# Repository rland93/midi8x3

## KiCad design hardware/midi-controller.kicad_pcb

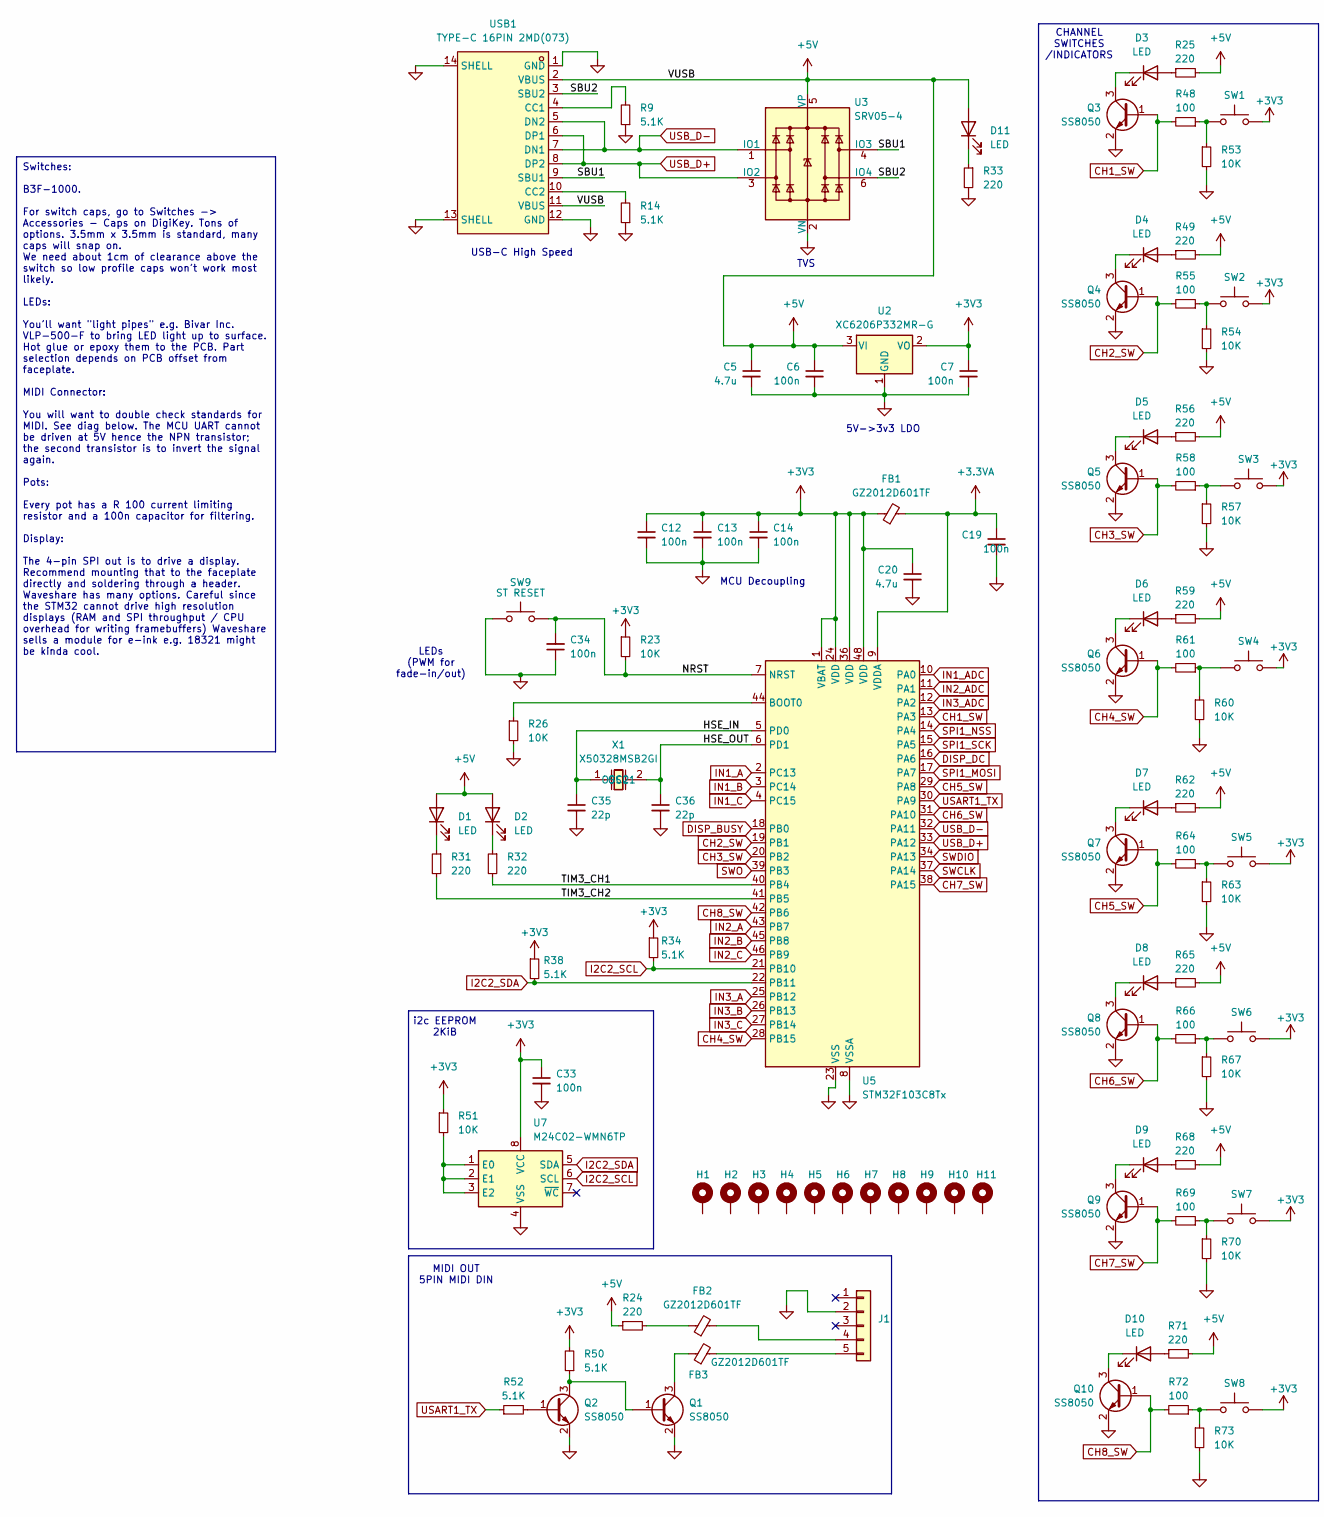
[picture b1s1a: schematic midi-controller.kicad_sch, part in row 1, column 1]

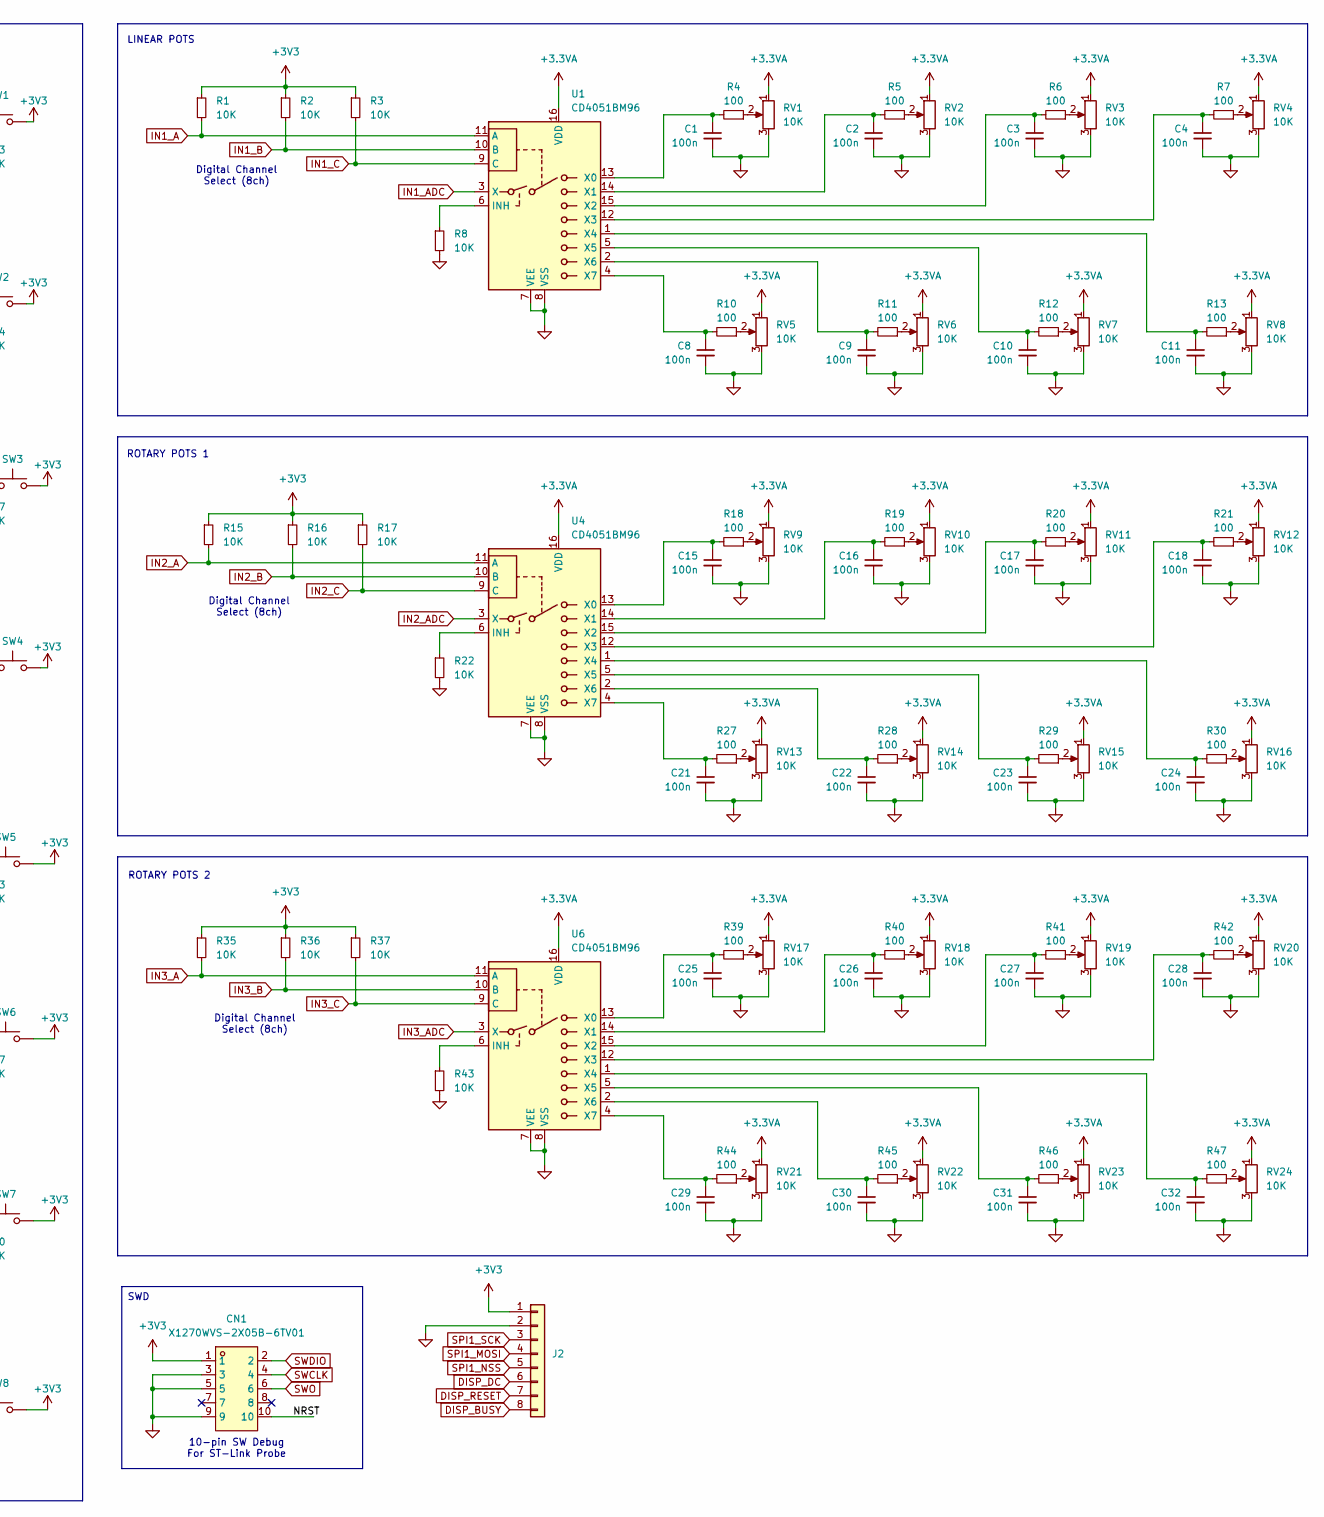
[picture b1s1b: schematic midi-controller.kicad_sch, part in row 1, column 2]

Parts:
C1, C2, C3, C4, C6, C7, C8, C9, C10, C11, C12, C13, C14, C15, C16, C17, C18, C19, C21, C22, C23, C24, C25, C26, C27, C28, C29, C30, C31, C32, C33, C34: 100n; C_0402_1005Metric; LCSC ID C14663
C5, C20: 4.7u; C_0603_1608Metric; LCSC ID C19666
C35, C36: 22p; C_0402_1005Metric
CN1: X1270WVS-2X05B-6TV01; IDC-SMD_10P-P1.27_X1270WVS-2X05B-6TV01; LCSC Part Extended
D1, D2, D3, D4, D5, D6, D7, D8, D9, D10, D11: LED; LED_0603_1608Metric; LCSC ID C2286
FB1, FB2, FB3: GZ2012D601TF; L_0805_2012Metric; LCSC ID C1017
H1, H2, H3, H4, H5, H6, H7, H8, H9, H10, H11: MountingHole_Pad; MountingHole_2.7mm_M2.5_DIN965_Pad
J1: Conn_01x05; PinHeader_1x05_P2.54mm_Vertical; LCSC ID None
J2: Conn_01x08; JST_PH_B8B-PH-K_1x08_P2.00mm_Vertical
Q1, Q2, Q3, Q4, Q5, Q6, Q7, Q8, Q9, Q10: SS8050; SOT-23; LCSC ID C2150
R1, R2, R3, R8, R15, R16, R17, R22, R23, R26, R35, R36, R37, R43, R51, R53, R54, R57, R60, R63, R67, R70, R73: 10K; R_0402_1005Metric; LCSC ID C25744
R4, R5, R6, R7, R10, R11, R12, R13, R18, R19, R20, R21, R27, R28, R29, R30, R39, R40, R41, R42, R44, R45, R46, R47, R48, R55, R58, R61, R64, R66, R69, R72: 100; R_0603_1608Metric; LCSC ID C22775
R9, R14, R34, R38, R50, R52: 5.1K; R_0402_1005Metric; LCSC ID C25905
R24, R25, R31, R32, R33, R49, R56, R59, R62, R65, R68, R71: 220; R_0603_1608Metric; LCSC ID C22962
RV1, RV2, RV3, RV4, RV5, RV6, RV7, RV8: 10K; Potentiometer_Bourns_PTA6043_Single_Slide; Digikey/Part PTA6043-2015DPB103
RV9, RV10, RV11, RV12, RV13, RV14, RV15, RV16, RV17, RV18, RV19, RV20, RV21, RV22, RV23, RV24: 10K; Potentiometer_Bourns_PTV09A-1_Single_Vertical; Digikey/Part PTV09A-4025S-A103
SW1, SW2, SW3, SW4, SW5, SW6, SW7, SW8: SW_Push; SW_TH_Tactile_Omron_B3F-10xx
SW9: ST RESET; SW_TH_Tactile_Omron_B3F-10xx; LCSC Part None
U1, U4, U6: CD4051BM96; SOIC-16_3.9x9.9mm_P1.27mm; LCSC ID C21379
U2: XC6206P332MR-G; SOT-23-3; LCSC ID C5446
U3: SRV05-4; SOT-23-6; LCSC ID C7420376
U5: STM32F103C8Tx; LQFP-48_7x7mm_P0.5mm; LCSC ID C8734
U7: M24C02-WMN6TP; SOIC-8_3.9x4.9mm_P1.27mm; LCSC ID C7562
USB1: TYPE-C 16PIN 2MD(073); USB-C-SMD_TYPE-C-6PIN-2MD-073; LCSC Part Extended
X1: X50328MSB2GI; CRYSTAL-SMD_L5.0-W3.2; LCSC Part C115962

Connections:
+3.3VA: C19.1, FB1.2, RV1.1, RV2.1, RV3.1, RV4.1, RV5.1, RV6.1, RV7.1, RV8.1, RV9.1, RV10.1, RV11.1, RV12.1, RV13.1, RV14.1, RV15.1, RV16.1, RV17.1, RV18.1, RV19.1, RV20.1, RV21.1, RV22.1, RV23.1, RV24.1, U1.16 (VDD), U4.16 (VDD), U5.9 (VDDA), U6.16 (VDD)
+3V3: C7.1, C12.1, C13.1, C14.1, C20.1, C33.1, CN1.1, FB1.1, J2.1, R1.1, R2.1, R3.1, R15.1, R16.1, R17.1, R23.1, R34.1, R35.1, R36.1, R37.1, R38.1, R50.2, R51.1, SW1.2, SW2.2, SW3.2, SW4.2, SW5.2, SW6.2, SW7.2, SW8.2, U2.2 (VO), U5.1 (VBAT), U5.24 (VDD), U5.36 (VDD), U5.48 (VDD), U7.8 (VCC)
+5V: C5.1, C6.1, D1.2 (A), D2.2 (A), D11.2 (A), R24.1, R25.2, R49.2, R56.2, R59.2, R62.2, R65.2, R68.2, R71.2, U2.3 (VI), U3.5 (VP), USB1.2 (VBUS), USB1.11 (VBUS)
/HSE_IN: C35.1, U5.5 (PD0), X1.1 (OSC1)
/HSE_OUT: C36.1, U5.6 (PD1), X1.2 (OSC2)
/NRST: C34.2, CN1.10, R23.2, SW9.2, U5.7 (NRST)
/SBU1: U3.4 (IO3), USB1.9 (SBU1)
/SBU2: U3.6 (IO4), USB1.3 (SBU2)
/TIM3_CH1: R32.2, U5.40 (PB4)
/TIM3_CH2: R31.2, U5.41 (PB5)
CH1_SW: Q3.1 (B), R48.2, U5.13 (PA3)
CH2_SW: Q4.1 (B), R55.2, U5.19 (PB1)
CH3_SW: Q5.1 (B), R58.2, U5.20 (PB2)
CH4_SW: Q6.1 (B), R61.2, U5.28 (PB15)
CH5_SW: Q7.1 (B), R64.2, U5.29 (PA8)
CH6_SW: Q8.1 (B), R66.2, U5.31 (PA10)
CH7_SW: Q9.1 (B), R69.2, U5.38 (PA15)
CH8_SW: Q10.1 (B), R72.2, U5.42 (PB6)
DISP_BUSY: J2.8, U5.18 (PB0)
DISP_DC: J2.6, U5.16 (PA6)
DISP_RESET: J2.7
GND: C1.2, C2.2, C3.2, C4.2, C5.2, C6.2, C7.2, C8.2, C9.2, C10.2, C11.2, C12.2, C13.2, C14.2, C15.2, C16.2, C17.2, C18.2, C19.2, C20.2, C21.2, C22.2, C23.2, C24.2, C25.2, C26.2, C27.2, C28.2, C29.2, C30.2, C31.2, C32.2, C33.2, C34.1, C35.2, C36.2, CN1.3, CN1.5, CN1.9, J1.2, J2.2, Q1.2 (E), Q2.2 (E), Q3.2 (E), Q4.2 (E), Q5.2 (E), Q6.2 (E), Q7.2 (E), Q8.2 (E), Q9.2 (E), Q10.2 (E), R8.2, R9.1, R14.1, R22.2, R26.2, R33.2, R43.2, R53.2, R54.2, R57.2, R60.2, R63.2, R67.2, R70.2, R73.2, RV1.3, RV2.3, RV3.3, RV4.3, RV5.3, RV6.3, RV7.3, RV8.3, RV9.3, RV10.3, RV11.3, RV12.3, RV13.3, RV14.3, RV15.3, RV16.3, RV17.3, RV18.3, RV19.3, RV20.3, RV21.3, RV22.3, RV23.3, RV24.3, SW9.1, U1.7 (VEE), U1.8 (VSS), U2.1 (GND), U3.2 (VN), U4.7 (VEE), U4.8 (VSS), U5.8 (VSSA), U5.23 (VSS), U5.35 (VSS), U5.47 (VSS), U6.7 (VEE), U6.8 (VSS), U7.4 (VSS), USB1.1 (GND), USB1.12 (GND), USB1.13 (SHELL), USB1.14 (SHELL)
I2C2_SCL: R34.2, U5.21 (PB10), U7.6 (SCL)
I2C2_SDA: R38.2, U5.22 (PB11), U7.5 (SDA)
IN1_A: R1.2, U1.11 (A), U5.2 (PC13)
IN1_ADC: U1.3 (X), U5.10 (PA0)
IN1_B: R2.2, U1.10 (B), U5.3 (PC14)
IN1_C: R3.2, U1.9 (C), U5.4 (PC15)
IN2_A: R15.2, U4.11 (A), U5.43 (PB7)
IN2_ADC: U4.3 (X), U5.11 (PA1)
IN2_B: R16.2, U4.10 (B), U5.45 (PB8)
IN2_C: R17.2, U4.9 (C), U5.46 (PB9)
IN3_A: R35.2, U5.25 (PB12), U6.11 (A)
IN3_ADC: U5.12 (PA2), U6.3 (X)
IN3_B: R36.2, U5.26 (PB13), U6.10 (B)
IN3_C: R37.2, U5.27 (PB14), U6.9 (C)
unnamed: D1.1 (K), R31.1
unnamed: D2.1 (K), R32.1
unnamed: D3.2 (A), R25.1
unnamed: D3.1 (K), Q3.3 (C)
unnamed: D4.2 (A), R49.1
unnamed: D4.1 (K), Q4.3 (C)
unnamed: D5.2 (A), R56.1
unnamed: D5.1 (K), Q5.3 (C)
unnamed: D6.2 (A), R59.1
unnamed: D6.1 (K), Q6.3 (C)
unnamed: D7.2 (A), R62.1
unnamed: D7.1 (K), Q7.3 (C)
unnamed: D8.2 (A), R65.1
unnamed: D8.1 (K), Q8.3 (C)
unnamed: D9.2 (A), R68.1
unnamed: D9.1 (K), Q9.3 (C)
unnamed: D10.2 (A), R71.1
unnamed: D10.1 (K), Q10.3 (C)
unnamed: D11.1 (K), R33.1
unnamed: FB2.1, R24.2
unnamed: FB2.2, J1.4
unnamed: FB3.2, J1.5
unnamed: Q1.1 (B), Q2.3 (C), R50.1
unnamed: FB3.1, Q1.3 (C)
unnamed: Q2.1 (B), R52.2
unnamed: R4.1, RV1.2
unnamed: R5.1, RV2.2
unnamed: R6.1, RV3.2
unnamed: R7.1, RV4.2
unnamed: R10.1, RV5.2
unnamed: R11.1, RV6.2
unnamed: R12.1, RV7.2
unnamed: R13.1, RV8.2
unnamed: R18.1, RV9.2
unnamed: R19.1, RV10.2
unnamed: R20.1, RV11.2
unnamed: R21.1, RV12.2
unnamed: R27.1, RV13.2
unnamed: R28.1, RV14.2
unnamed: R29.1, RV15.2
unnamed: R30.1, RV16.2
unnamed: R39.1, RV17.2
unnamed: R40.1, RV18.2
unnamed: R41.1, RV19.2
unnamed: R42.1, RV20.2
unnamed: R44.1, RV21.2
unnamed: R45.1, RV22.2
unnamed: R46.1, RV23.2
unnamed: R47.1, RV24.2
unnamed: R48.1, R53.1, SW1.1
unnamed: R54.1, R55.1, SW2.1
unnamed: R57.1, R58.1, SW3.1
unnamed: R60.1, R61.1, SW4.1
unnamed: R63.1, R64.1, SW5.1
unnamed: R66.1, R67.1, SW6.1
unnamed: R69.1, R70.1, SW7.1
unnamed: R72.1, R73.1, SW8.1
unnamed: R8.1, U1.6 (INH)
unnamed: C1.1, R4.2, U1.13 (X0)
unnamed: C2.1, R5.2, U1.14 (X1)
unnamed: C3.1, R6.2, U1.15 (X2)
unnamed: C4.1, R7.2, U1.12 (X3)
unnamed: C11.1, R13.2, U1.1 (X4)
unnamed: C10.1, R12.2, U1.5 (X5)
unnamed: C9.1, R11.2, U1.2 (X6)
unnamed: C8.1, R10.2, U1.4 (X7)
unnamed: R22.1, U4.6 (INH)
unnamed: C15.1, R18.2, U4.13 (X0)
unnamed: C16.1, R19.2, U4.14 (X1)
unnamed: C17.1, R20.2, U4.15 (X2)
unnamed: C18.1, R21.2, U4.12 (X3)
unnamed: C24.1, R30.2, U4.1 (X4)
unnamed: C23.1, R29.2, U4.5 (X5)
unnamed: C22.1, R28.2, U4.2 (X6)
unnamed: C21.1, R27.2, U4.4 (X7)
unnamed: R26.1, U5.44 (BOOT0)
unnamed: R43.1, U6.6 (INH)
unnamed: C25.1, R39.2, U6.13 (X0)
unnamed: C26.1, R40.2, U6.14 (X1)
unnamed: C27.1, R41.2, U6.15 (X2)
unnamed: C28.1, R42.2, U6.12 (X3)
unnamed: C32.1, R47.2, U6.1 (X4)
unnamed: C31.1, R46.2, U6.5 (X5)
unnamed: C30.1, R45.2, U6.2 (X6)
unnamed: C29.1, R44.2, U6.4 (X7)
unnamed: R51.2, U7.1 (E0), U7.2 (E1), U7.3 (E2)
unnamed: R9.2, USB1.4 (CC1)
unnamed: R14.2, USB1.10 (CC2)
SPI1_MOSI: J2.4, U5.17 (PA7)
SPI1_NSS: J2.5, U5.14 (PA4)
SPI1_SCK: J2.3, U5.15 (PA5)
SWCLK: CN1.4, U5.37 (PA14)
SWDIO: CN1.2, U5.34 (PA13)
SWO: CN1.6, U5.39 (PB3)
USART1_TX: R52.1, U5.30 (PA9)
USB_D+: U3.3 (IO2), U5.33 (PA12), USB1.6 (DP1), USB1.8 (DP2)
USB_D-: U3.1 (IO1), U5.32 (PA11), USB1.5 (DN2), USB1.7 (DN1)

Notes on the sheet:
Switches: B3F-1000. For switch caps, go to Switches -> Accessories - Caps on DigiKey. Tons of options. 3.5mm x 3.5mm is standard, many caps will snap on. We need about 1cm of clearance above the switch so low profile caps won't work most likely. LEDs: You'll want "light pipes" e.g. Bivar Inc. VLP-5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
Digital Channel Select (8ch)
LEDs (PWM for fade-in/out)
CHANNEL SWITCHES /INDICATORS
10-pin SW Debug For ST-Link Probe
ROTARY POTS 2
i2c EEPROM 2KiB
USB-C High Speed
LINEAR POTS
MCU Decoupling
SWD
MIDI OUT 5PIN MIDI DIN
TVS
ROTARY POTS 1
5V->3v3 LDO

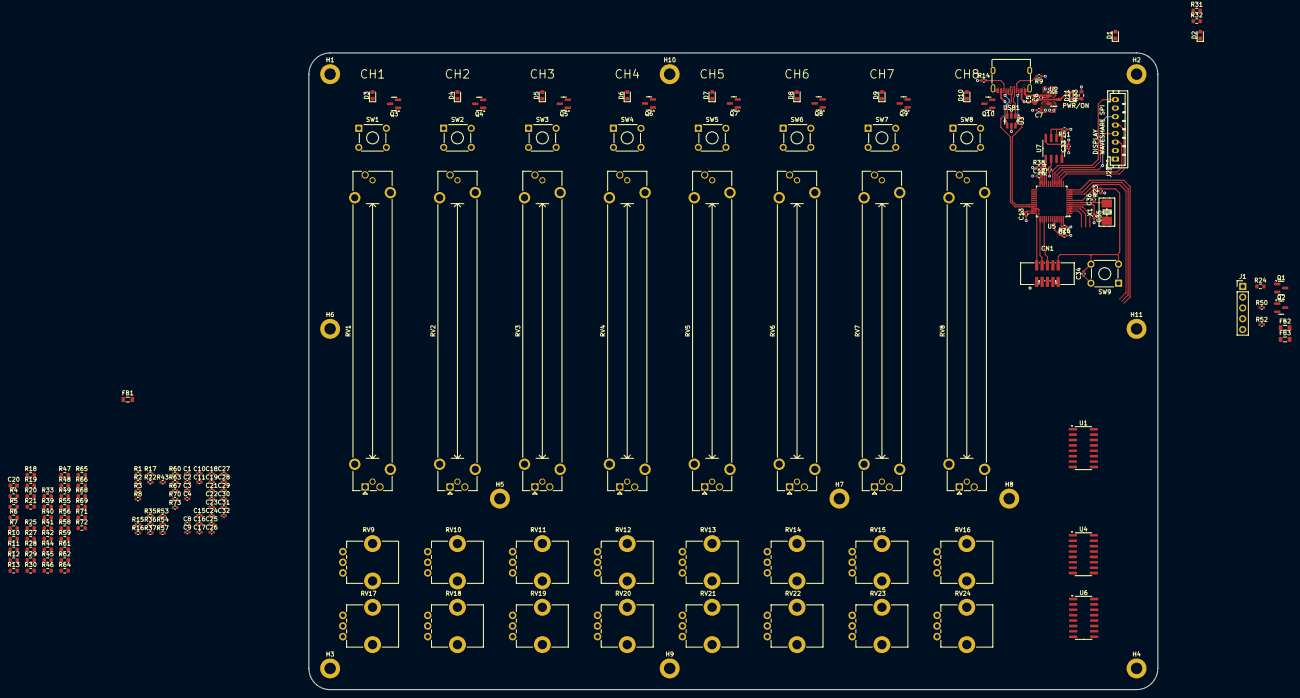
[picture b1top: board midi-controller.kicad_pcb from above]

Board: 4 copper layers, 200.0 x 150.0 mm, 190 parts (0 on the bottom side), 132 nets.

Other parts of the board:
R33#2: 100; R_0603_1608Metric

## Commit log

2024-12-17 gitignore
2024-12-17 board
